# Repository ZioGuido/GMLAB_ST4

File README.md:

# GMLAB_ST4
Repository for GMLAB ST4 - Switchable Thru-box

ST4 is a "Four port Swtichable Thru Box", practically an easy and simple Midi Router, useful to control up to four synthesizers (or other MIDI devices) from one keyboard and switch quickly between them. Imagine you have one keyboard and up to four sound modules (synthesizers, drum machines, samplers, expanders, etc.) and you want to select which one you want to play from your keyboard. Just push the correspondent button and play, in any combination you like. The advantage of this box is that it will take into account notes still playing when the buttons are turned off, in order to avoid unwanted hung notes or incomplete Midi events. It can also function as a Usb-Midi interface.

Buy it in kit or preassembled at www.GMLAB.it

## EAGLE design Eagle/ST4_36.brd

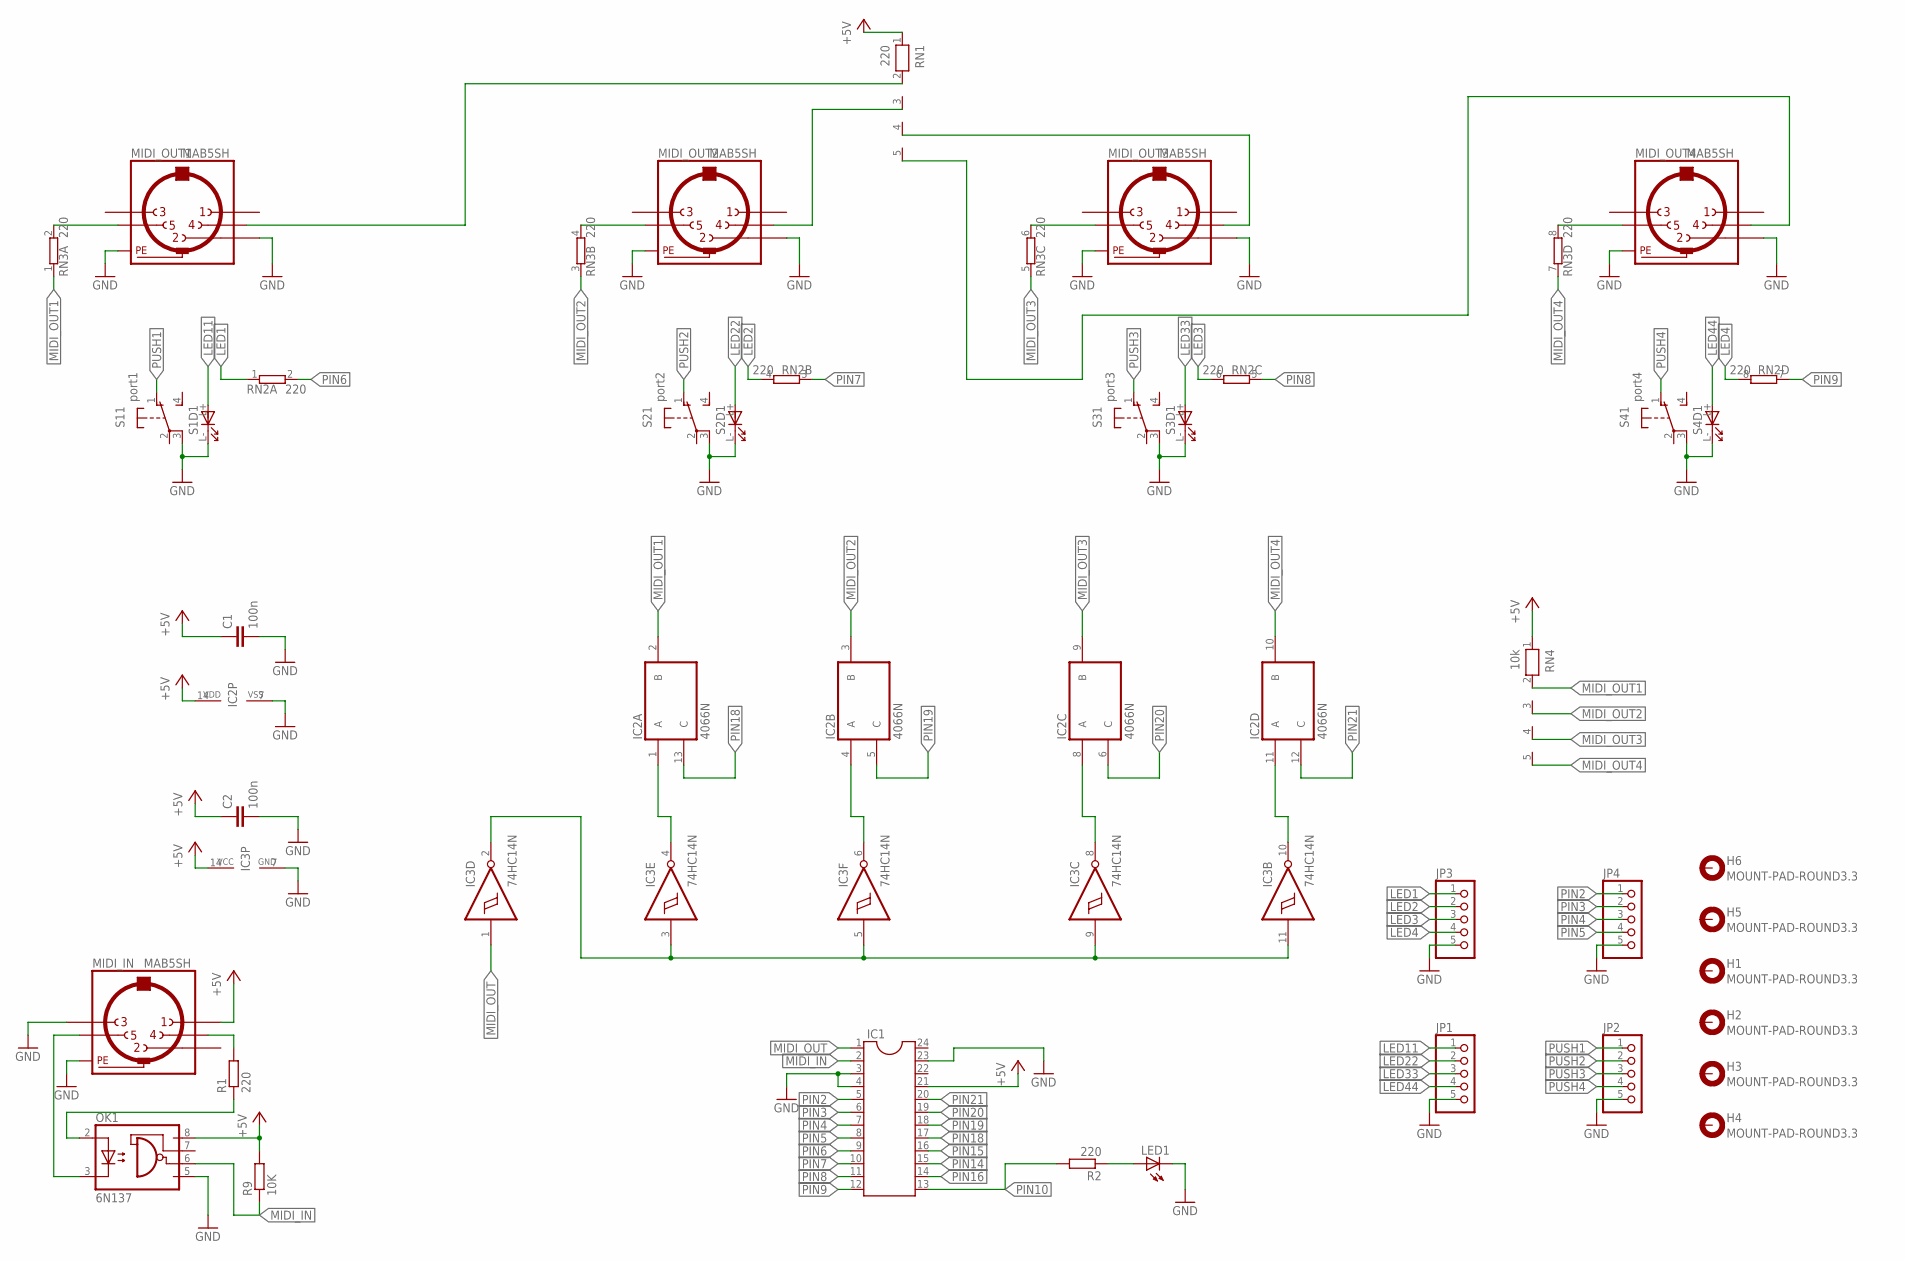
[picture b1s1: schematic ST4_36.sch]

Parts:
C1, C2: 100n; C050-024X044
H1, H2, H3, H4, H5, H6: MOUNT-PAD-ROUND3.3; 3,3-PAD
IC1: DIL24-6
IC2: 4066N; DIL14
IC3: 74HC14N; DIL14
JP1, JP2, JP3, JP4: PINHD-1X5; 1X05
LED1: LED_LED3MM
MIDI_IN: MAB5SH
MIDI_OUT1, MIDI_OUT2, MIDI_OUT3, MIDI_OUT4: MAB5SH
OK1: 6N137; DIL08
R1, R2: 220; 0207/7
R9: 10K; 0207/7
RN1: 220; RN-5
RN2, RN3: 220; SIL8
RN4: 10k; RN-5
S1: port1; SPLG1YCS0014
S2: port2; SPLG1YCS0014
S3: port3; SPLG1YCS0014
S4: port4; SPLG1YCS0014

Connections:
+5V: C1.1, C2.1, IC1.21, IC2.14 (VDD), IC3.14 (VCC), MIDI_IN.1, OK1.8 (VCC), R9.2, RN1.1, RN4.1
GND: C1.2, C2.2, IC1.3, IC1.4, IC1.23, IC2.7 (VSS), IC3.7 (GND), JP1.5, JP2.5, JP3.5, JP4.5, LED1.K (C), MIDI_IN.3, MIDI_IN.PE, MIDI_IN.PE@ (PE), MIDI_OUT1.2, MIDI_OUT1.PE, MIDI_OUT1.PE@ (PE), MIDI_OUT2.2, MIDI_OUT2.PE, MIDI_OUT2.PE@ (PE), MIDI_OUT3.2, MIDI_OUT3.PE, MIDI_OUT3.PE@ (PE), MIDI_OUT4.2, MIDI_OUT4.PE, MIDI_OUT4.PE@ (PE), OK1.5 (GND), S1.3, S1.L- (C), S2.3, S2.L- (C), S3.3, S3.L- (C), S4.3, S4.L- (C)
LED1: JP3.1, RN2.1
LED2: JP3.2, RN2.4 (2)
LED3: JP3.3, RN2.6 (2)
LED4: JP3.4, RN2.8 (2)
LED11: JP1.1, S1.L+ (A)
LED22: JP1.2, S2.L+ (A)
LED33: JP1.3, S3.L+ (A)
LED44: JP1.4, S4.L+ (A)
MIDI_IN: IC1.2, OK1.6 (VO), R9.1
MIDI_OUT: IC1.1, IC3.1 (I)
MIDI_OUT1: IC2.2 (B), RN3.1, RN4.2
MIDI_OUT2: IC2.3 (B), RN3.3 (1), RN4.3
MIDI_OUT3: IC2.9 (B), RN3.5 (1), RN4.4
MIDI_OUT4: IC2.10 (B), RN3.7 (1), RN4.5
unnamed: MIDI_OUT2.5, RN3.4 (2)
unnamed: MIDI_OUT3.5, RN3.6 (2)
unnamed: MIDI_OUT4.5, RN3.8 (2)
unnamed: MIDI_OUT4.4, RN1.5
unnamed: MIDI_IN.5, OK1.3 (C)
unnamed: OK1.2 (A), R1.1
unnamed: MIDI_IN.4, R1.2
unnamed: MIDI_OUT1.5, RN3.2
unnamed: MIDI_OUT2.4, RN1.3
unnamed: MIDI_OUT1.4, RN1.2
unnamed: MIDI_OUT3.4, RN1.4
unnamed: LED1.A, R2.1
unnamed: IC3.2 (O), IC3.3 (I), IC3.5 (I), IC3.9 (I), IC3.11 (I)
unnamed: IC2.1 (A), IC3.4 (O)
unnamed: IC2.4 (A), IC3.6 (O)
unnamed: IC2.8 (A), IC3.8 (O)
unnamed: IC2.11 (A), IC3.10 (O)
PIN2: IC1.5, JP4.1
PIN3: IC1.6, JP4.2
PIN4: IC1.7, JP4.3
PIN5: IC1.8, JP4.4
PIN6: IC1.9, RN2.2
PIN7: IC1.10, RN2.3 (1)
PIN8: IC1.11, RN2.5 (1)
PIN9: IC1.12, RN2.7 (1)
PIN10: IC1.13, R2.2
PIN14: IC1.15
PIN15: IC1.16
PIN16: IC1.14
PIN18: IC1.17, IC2.13 (C)
PIN19: IC1.18, IC2.5 (C)
PIN20: IC1.19, IC2.6 (C)
PIN21: IC1.20, IC2.12 (C)
PUSH1: JP2.1, S1.1 (O)
PUSH2: JP2.2, S2.1 (O)
PUSH3: JP2.3, S3.1 (O)
PUSH4: JP2.4, S4.1 (O)

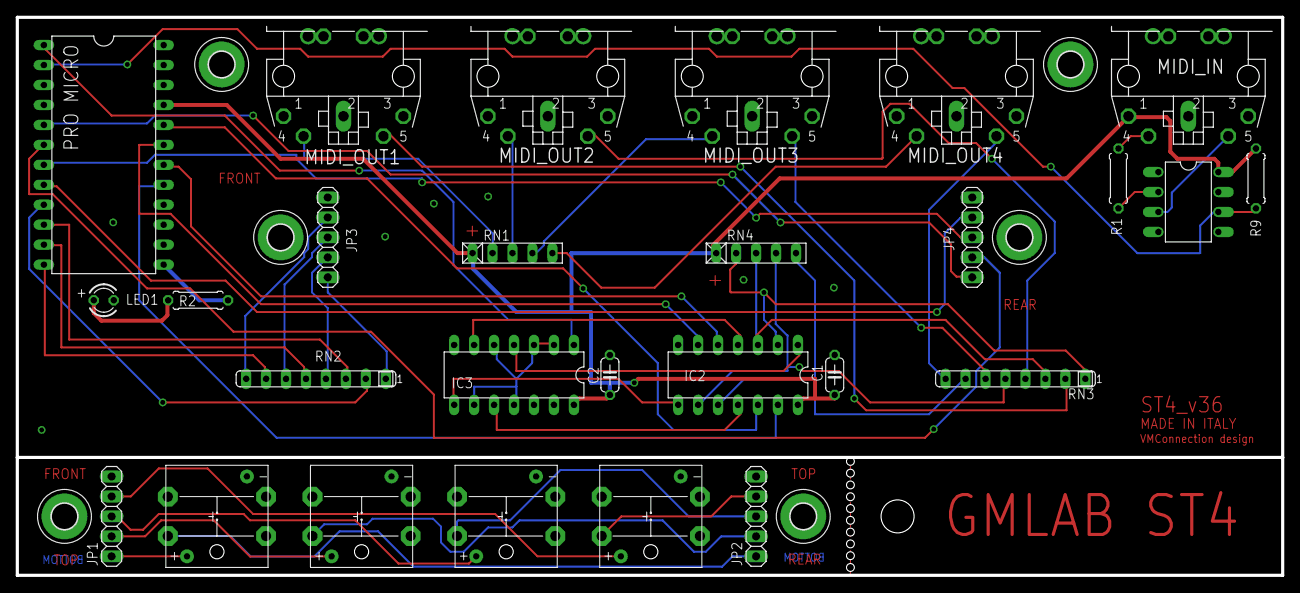
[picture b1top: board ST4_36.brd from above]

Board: 2 copper layers, 161.0 x 71.0 mm, 33 parts (0 on the bottom side), 50 nets.

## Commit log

2021-02-16 Added USB Midi Out linked to OUT#1
2022-05-09 Fixed component list
